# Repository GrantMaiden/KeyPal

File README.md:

KeyPal is A project I worked with during my undergrad alongside my teammates, Dane Le, Justin Warner, and Spencer Anderson.

I was the only EE working on the project, so my main duties were to develop the schematic and PCB for the group. I also developed the MCU application, and took care of component selection as well as analyzed and timing constraints on the system.

KeyPal is a fun solution to helping teach a new typist the ins and outs of proper keyboard hand placement.
It has capacitive sensors in the homerow of the keyboard, to make sure that proper hand placement is intact during typing, as well as multicolor LEDs under every key on the keyboard. These light up to aid the typist in learning the keypositions while using the peripheral typing trainer application, which is written in python.

________________________________________________________________________________________________________________________

Schematic creation, PCB layout, component selection, MCU design, C/C++, Python, timing analysis, Communication Protocols (i2c, USB),  capacitive touch.

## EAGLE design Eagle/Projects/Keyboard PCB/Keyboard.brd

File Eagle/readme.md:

Eagle Files and Libraries

Place in Users\<USER>\Documents\eagle

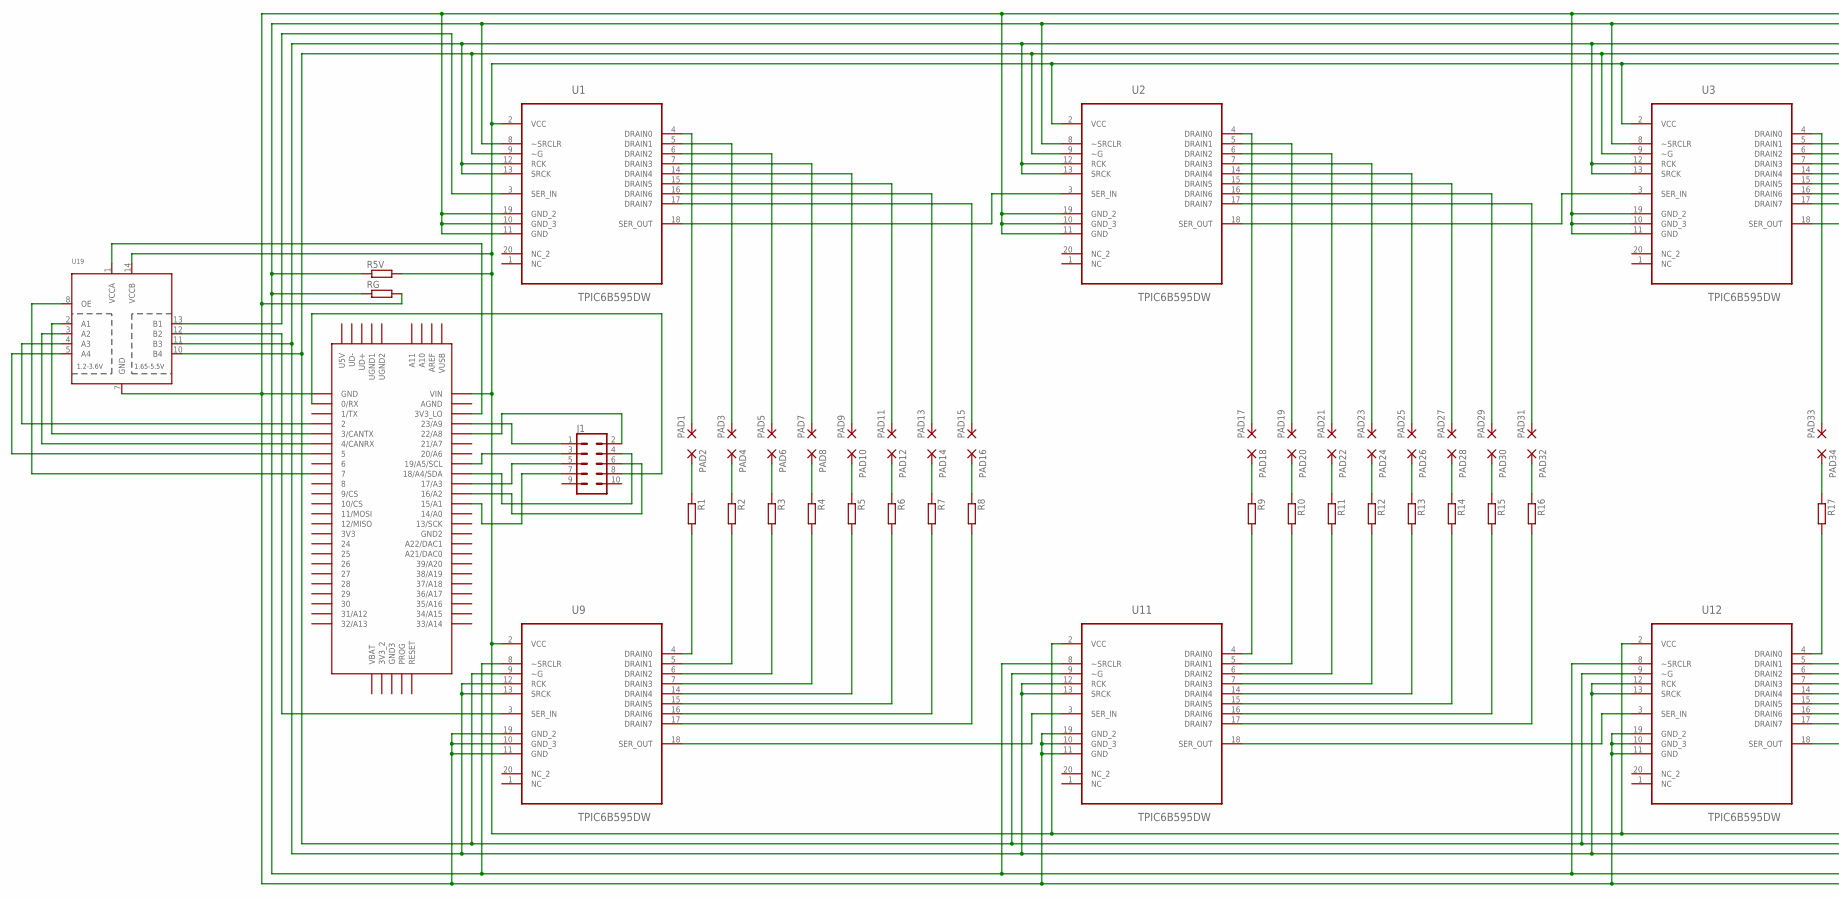
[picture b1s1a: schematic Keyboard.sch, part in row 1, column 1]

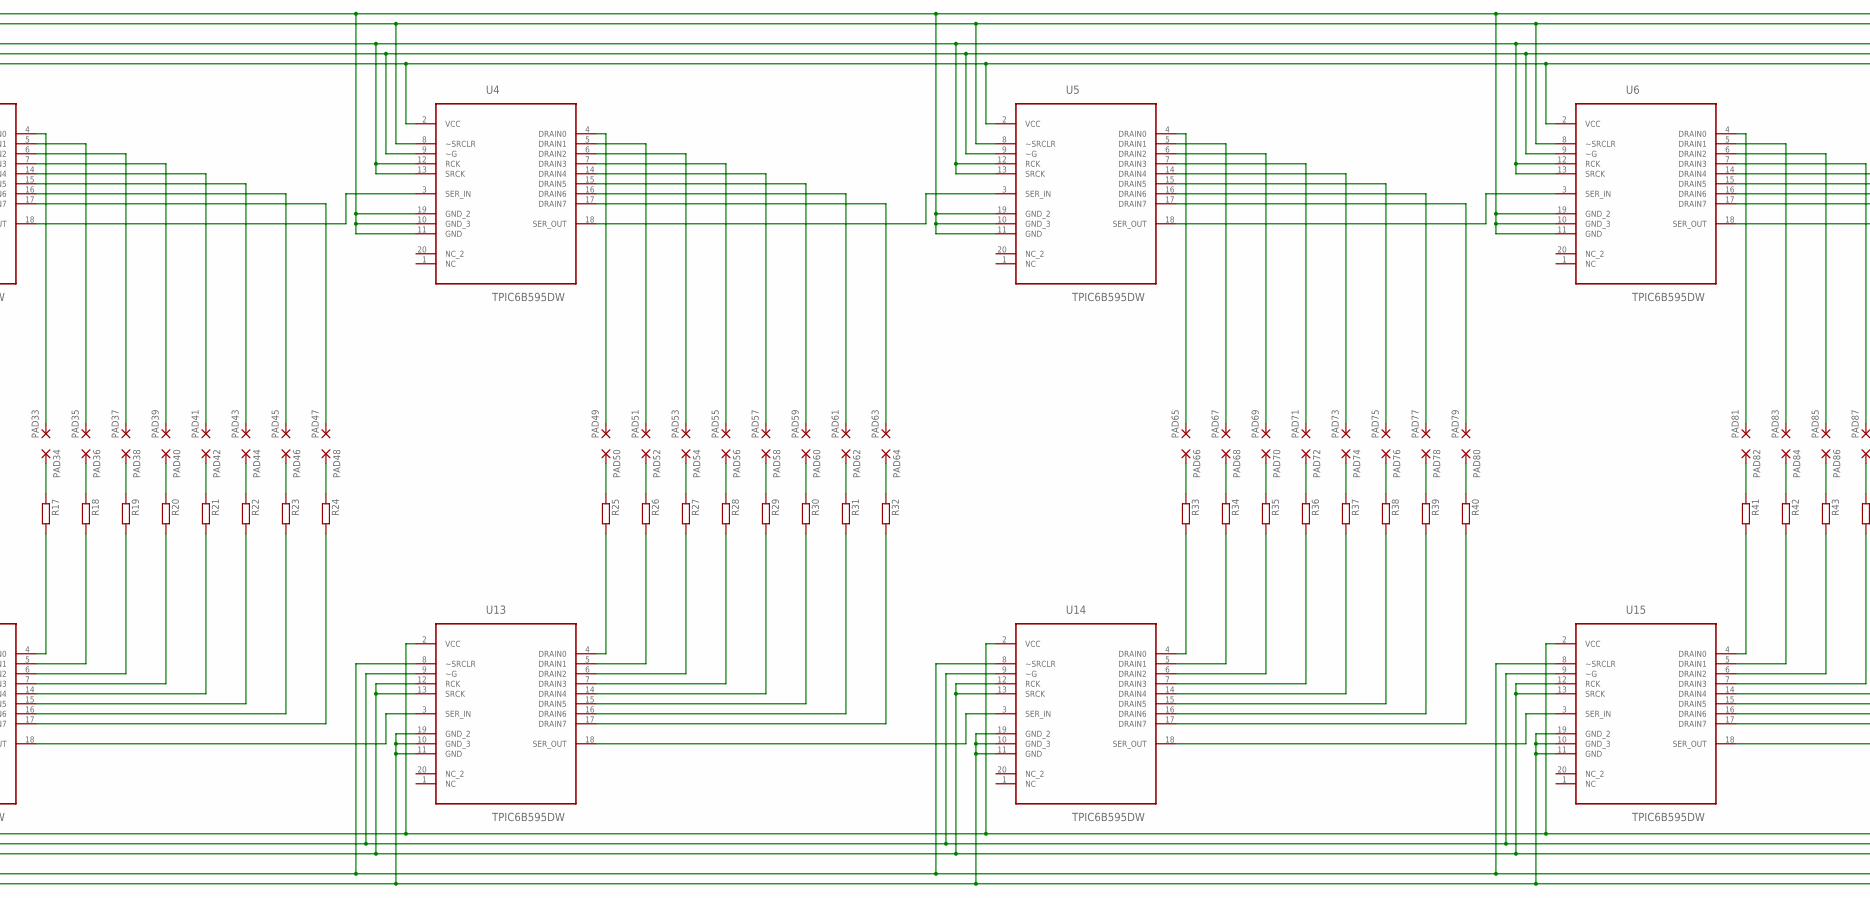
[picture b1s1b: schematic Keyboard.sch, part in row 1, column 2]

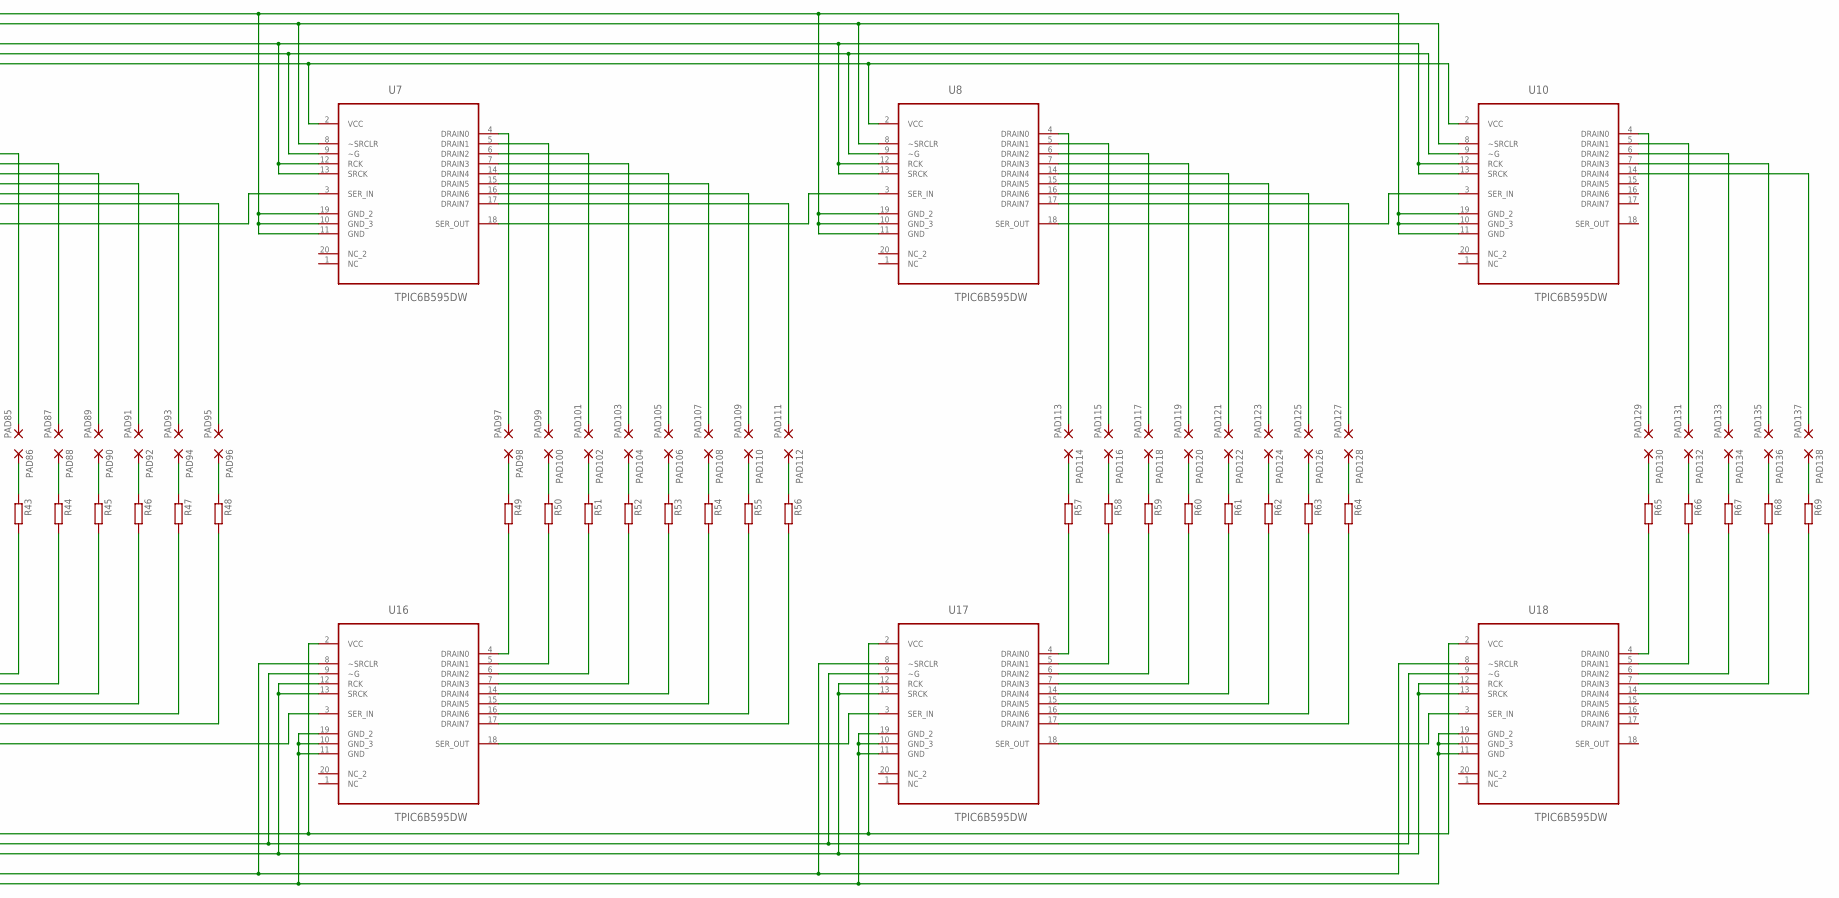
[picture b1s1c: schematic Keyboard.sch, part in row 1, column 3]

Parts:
J1: CONN_05X2SHD; 2X5-SHROUDED
PAD1, PAD2, PAD3, PAD4, PAD5, PAD6, PAD7, PAD8, PAD9, PAD10, PAD11, PAD12, PAD13, PAD14, PAD15, PAD16, PAD17, PAD18, PAD19, PAD20, PAD21, PAD22, PAD23, PAD24, PAD25, PAD26, PAD27, PAD28, PAD29, PAD30, PAD31, PAD32, PAD33, PAD34, PAD35, PAD36, PAD37, PAD38, PAD39, PAD40, PAD41, PAD42, PAD43, PAD44, PAD45, PAD46, PAD47, PAD48, PAD49, PAD50, PAD51, PAD52, PAD53, PAD54, PAD55, PAD56, PAD57, PAD58, PAD59, PAD60, PAD61, PAD62, PAD63, PAD64, PAD65, PAD66, PAD67, PAD68, PAD69, PAD70, PAD71, PAD72, PAD73, PAD74, PAD75, PAD76, PAD77, PAD78, PAD79, PAD80, PAD81, PAD82, PAD83, PAD84, PAD85, PAD86, PAD87, PAD88, PAD89, PAD90, PAD91, PAD92, PAD93, PAD94, PAD95, PAD96, PAD97, PAD98, PAD99, PAD100, PAD101, PAD102, PAD103, PAD104, PAD105, PAD106, PAD107, PAD108, PAD109, PAD110, PAD111, PAD112, PAD113, PAD114, PAD115, PAD116, PAD117, PAD118, PAD119, PAD120, PAD121, PAD122, PAD123, PAD124, PAD125, PAD126, PAD127, PAD128, PAD129, PAD130, PAD131, PAD132, PAD133, PAD134, PAD135, PAD136, PAD137, PAD138: 1,6/0,8
R1, R2, R3, R4, R5, R5V, R6, R7, R8, R9, R10, R11, R12, R13, R14, R15, R16, R17, R18, R19, R20, R21, R22, R23, R24, R25, R26, R27, R28, R29, R30, R31, R32, R33, R34, R35, R36, R37, R38, R39, R40, R41, R42, R43, R44, R45, R46, R47, R48, R49, R50, R51, R52, R53, R54, R55, R56, R57, R58, R59, R60, R61, R62, R63, R64, R65, R66, R67, R68, R69: R; R0805
RG: R; R0805
U1, U2, U3, U4, U5, U6, U7, U8, U9, U10, U11, U12, U13, U14, U15, U16, U17, U18: TPIC6B595DW; SOIC127P1030X265-20N
U19: TXB0104PWRSOIC14; SO14
U$59: TEENSY_3.5/3.6

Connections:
unnamed: PAD2.1, R1.1
unnamed: U1.18 (SER_OUT), U2.3 (SER_IN)
unnamed: U1.12 (RCK), U1.13 (SRCK), U2.12 (RCK), U2.13 (SRCK), U3.12 (RCK), U3.13 (SRCK), U4.12 (RCK), U4.13 (SRCK), U5.12 (RCK), U5.13 (SRCK), U6.12 (RCK), U6.13 (SRCK), U7.12 (RCK), U7.13 (SRCK), U8.12 (RCK), U8.13 (SRCK), U9.12 (RCK), U9.13 (SRCK), U10.12 (RCK), U10.13 (SRCK), U11.12 (RCK), U11.13 (SRCK), U12.12 (RCK), U12.13 (SRCK), U13.12 (RCK), U13.13 (SRCK), U14.12 (RCK), U14.13 (SRCK), U15.12 (RCK), U15.13 (SRCK), U16.12 (RCK), U16.13 (SRCK), U17.12 (RCK), U17.13 (SRCK), U18.12 (RCK), U18.13 (SRCK), U19.11 (B3)
unnamed: PAD4.1, R2.1
unnamed: PAD6.1, R3.1
unnamed: PAD8.1, R4.1
unnamed: PAD10.1, R5.1
unnamed: PAD12.1, R6.1
unnamed: PAD14.1, R7.1
unnamed: PAD16.1, R8.1
unnamed: PAD18.1, R9.1
unnamed: U1.9 (~G), U2.9 (~G), U3.9 (~G), U4.9 (~G), U5.9 (~G), U6.9 (~G), U7.9 (~G), U8.9 (~G), U9.9 (~G), U10.9 (~G), U11.9 (~G), U12.9 (~G), U13.9 (~G), U14.9 (~G), U15.9 (~G), U16.9 (~G), U17.9 (~G), U18.9 (~G), U19.10 (B4)
unnamed: PAD20.1, R10.1
unnamed: PAD22.1, R11.1
unnamed: PAD24.1, R12.1
unnamed: PAD26.1, R13.1
unnamed: PAD28.1, R14.1
unnamed: PAD30.1, R15.1
unnamed: PAD32.1, R16.1
unnamed: PAD34.1, R17.1
unnamed: PAD36.1, R18.1
unnamed: PAD38.1, R19.1
unnamed: PAD40.1, R20.1
unnamed: PAD42.1, R21.1
unnamed: PAD44.1, R22.1
unnamed: PAD46.1, R23.1
unnamed: PAD48.1, R24.1
unnamed: PAD50.1, R25.1
unnamed: PAD52.1, R26.1
unnamed: PAD54.1, R27.1
unnamed: PAD56.1, R28.1
unnamed: PAD58.1, R29.1
unnamed: PAD60.1, R30.1
unnamed: PAD62.1, R31.1
unnamed: PAD64.1, R32.1
unnamed: PAD66.1, R33.1
unnamed: PAD68.1, R34.1
unnamed: PAD70.1, R35.1
unnamed: PAD72.1, R36.1
unnamed: PAD74.1, R37.1
unnamed: PAD76.1, R38.1
unnamed: PAD78.1, R39.1
unnamed: PAD80.1, R40.1
unnamed: PAD82.1, R41.1
unnamed: PAD84.1, R42.1
unnamed: PAD86.1, R43.1
unnamed: PAD88.1, R44.1
unnamed: PAD90.1, R45.1
unnamed: PAD92.1, R46.1
unnamed: PAD94.1, R47.1
unnamed: PAD96.1, R48.1
unnamed: PAD98.1, R49.1
unnamed: PAD100.1, R50.1
unnamed: PAD102.1, R51.1
unnamed: PAD104.1, R52.1
unnamed: PAD106.1, R53.1
unnamed: PAD108.1, R54.1
unnamed: PAD110.1, R55.1
unnamed: PAD112.1, R56.1
unnamed: PAD114.1, R57.1
unnamed: R5V.2, U1.2 (VCC), U2.2 (VCC), U3.2 (VCC), U4.2 (VCC), U5.2 (VCC), U6.2 (VCC), U7.2 (VCC), U8.2 (VCC), U9.2 (VCC), U10.2 (VCC), U11.2 (VCC), U12.2 (VCC), U13.2 (VCC), U14.2 (VCC), U15.2 (VCC), U16.2 (VCC), U17.2 (VCC), U18.2 (VCC), U19.14 (VCCB), U$59.VIN
unnamed: U19.4 (A3), U$59.2
unnamed: R5V.1, RG.1, U1.8 (~SRCLR), U2.8 (~SRCLR), U3.8 (~SRCLR), U4.8 (~SRCLR), U5.8 (~SRCLR), U6.8 (~SRCLR), U7.8 (~SRCLR), U8.8 (~SRCLR), U9.8 (~SRCLR), U10.8 (~SRCLR), U11.8 (~SRCLR), U12.8 (~SRCLR), U13.8 (~SRCLR), U14.8 (~SRCLR), U15.8 (~SRCLR), U16.8 (~SRCLR), U17.8 (~SRCLR), U18.8 (~SRCLR)
unnamed: U1.3 (SER_IN), U19.13 (B1)
unnamed: U2.18 (SER_OUT), U3.3 (SER_IN)
unnamed: R68.2, U18.7 (DRAIN3)
unnamed: R69.2, U18.14 (DRAIN4)
unnamed: PAD129.1, U10.4 (DRAIN0)
unnamed: PAD131.1, U10.5 (DRAIN1)
unnamed: U3.18 (SER_OUT), U4.3 (SER_IN)
unnamed: U4.18 (SER_OUT), U5.3 (SER_IN)
unnamed: U5.18 (SER_OUT), U6.3 (SER_IN)
unnamed: U6.18 (SER_OUT), U7.3 (SER_IN)
unnamed: U7.18 (SER_OUT), U8.3 (SER_IN)
unnamed: U8.18 (SER_OUT), U10.3 (SER_IN)
unnamed: U19.1 (VCCA), U$59.3V3_LO
unnamed: U19.2 (A1), U$59.3/CANTX
unnamed: U9.3 (SER_IN), U19.12 (B2)
unnamed: U19.8 (OE), U$59.7
unnamed: PAD116.1, R58.1
unnamed: PAD118.1, R59.1
unnamed: PAD120.1, R60.1
unnamed: PAD122.1, R61.1
unnamed: PAD124.1, R62.1
unnamed: PAD126.1, R63.1
unnamed: PAD128.1, R64.1
unnamed: U9.18 (SER_OUT), U11.3 (SER_IN)
unnamed: U11.18 (SER_OUT), U12.3 (SER_IN)
unnamed: U12.18 (SER_OUT), U13.3 (SER_IN)
unnamed: U13.18 (SER_OUT), U14.3 (SER_IN)
unnamed: U14.18 (SER_OUT), U15.3 (SER_IN)
unnamed: U15.18 (SER_OUT), U16.3 (SER_IN)
unnamed: U16.18 (SER_OUT), U17.3 (SER_IN)
unnamed: U17.18 (SER_OUT), U18.3 (SER_IN)
unnamed: RG.2, U1.10 (GND_3), U1.11 (GND), U1.19 (GND_2), U2.10 (GND_3), U2.11 (GND), U2.19 (GND_2), U3.10 (GND_3), U3.11 (GND), U3.19 (GND_2), U4.10 (GND_3), U4.11 (GND), U4.19 (GND_2), U5.10 (GND_3), U5.11 (GND), U5.19 (GND_2), U6.10 (GND_3), U6.11 (GND), U6.19 (GND_2), U7.10 (GND_3), U7.11 (GND), U7.19 (GND_2), U8.10 (GND_3), U8.11 (GND), U8.19 (GND_2), U9.10 (GND_3), U9.11 (GND), U9.19 (GND_2), U10.10 (GND_3), U10.11 (GND), U10.19 (GND_2), U11.10 (GND_3), U11.11 (GND), U11.19 (GND_2), U12.10 (GND_3), U12.11 (GND), U12.19 (GND_2), U13.10 (GND_3), U13.11 (GND), U13.19 (GND_2), U14.10 (GND_3), U14.11 (GND), U14.19 (GND_2), U15.10 (GND_3), U15.11 (GND), U15.19 (GND_2), U16.10 (GND_3), U16.11 (GND), U16.19 (GND_2), U17.10 (GND_3), U17.11 (GND), U17.19 (GND_2), U18.10 (GND_3), U18.11 (GND), U18.19 (GND_2), U19.7 (GND), U$59.GND
unnamed: U19.5 (A4), U$59.5
unnamed: PAD130.1, R65.1
unnamed: PAD1.1, U1.4 (DRAIN0)
unnamed: PAD3.1, U1.5 (DRAIN1)
unnamed: PAD5.1, U1.6 (DRAIN2)
unnamed: PAD7.1, U1.7 (DRAIN3)
unnamed: PAD9.1, U1.14 (DRAIN4)
unnamed: PAD11.1, U1.15 (DRAIN5)
unnamed: PAD13.1, U1.16 (DRAIN6)
unnamed: PAD15.1, U1.17 (DRAIN7)
unnamed: R1.2, U9.4 (DRAIN0)
unnamed: R2.2, U9.5 (DRAIN1)
unnamed: R3.2, U9.6 (DRAIN2)
unnamed: R4.2, U9.7 (DRAIN3)
unnamed: R5.2, U9.14 (DRAIN4)
unnamed: R6.2, U9.15 (DRAIN5)
unnamed: R7.2, U9.16 (DRAIN6)
unnamed: R8.2, U9.17 (DRAIN7)
unnamed: R9.2, U11.4 (DRAIN0)
unnamed: R10.2, U11.5 (DRAIN1)
unnamed: R11.2, U11.6 (DRAIN2)
unnamed: R12.2, U11.7 (DRAIN3)
unnamed: R13.2, U11.14 (DRAIN4)
unnamed: R14.2, U11.15 (DRAIN5)
unnamed: R15.2, U11.16 (DRAIN6)
unnamed: R16.2, U11.17 (DRAIN7)
unnamed: PAD17.1, U2.4 (DRAIN0)
unnamed: PAD19.1, U2.5 (DRAIN1)
unnamed: PAD21.1, U2.6 (DRAIN2)
unnamed: PAD23.1, U2.7 (DRAIN3)
unnamed: PAD25.1, U2.14 (DRAIN4)
unnamed: PAD27.1, U2.15 (DRAIN5)
unnamed: PAD29.1, U2.16 (DRAIN6)
unnamed: PAD31.1, U2.17 (DRAIN7)
unnamed: PAD33.1, U3.4 (DRAIN0)
unnamed: PAD35.1, U3.5 (DRAIN1)
unnamed: PAD37.1, U3.6 (DRAIN2)
unnamed: PAD39.1, U3.7 (DRAIN3)
unnamed: PAD41.1, U3.14 (DRAIN4)
unnamed: PAD43.1, U3.15 (DRAIN5)
unnamed: PAD45.1, U3.16 (DRAIN6)
unnamed: PAD47.1, U3.17 (DRAIN7)
unnamed: R17.2, U12.4 (DRAIN0)
unnamed: R18.2, U12.5 (DRAIN1)
unnamed: R19.2, U12.6 (DRAIN2)
unnamed: R20.2, U12.7 (DRAIN3)
unnamed: R21.2, U12.14 (DRAIN4)
unnamed: R22.2, U12.15 (DRAIN5)
unnamed: R23.2, U12.16 (DRAIN6)
unnamed: R24.2, U12.17 (DRAIN7)
unnamed: R25.2, U13.4 (DRAIN0)
unnamed: R26.2, U13.5 (DRAIN1)
unnamed: R27.2, U13.6 (DRAIN2)
unnamed: U19.3 (A2), U$59.4/CANRX
unnamed: R28.2, U13.7 (DRAIN3)
unnamed: R29.2, U13.14 (DRAIN4)
unnamed: R30.2, U13.15 (DRAIN5)
unnamed: R31.2, U13.16 (DRAIN6)
unnamed: R32.2, U13.17 (DRAIN7)
unnamed: PAD49.1, U4.4 (DRAIN0)
unnamed: PAD51.1, U4.5 (DRAIN1)
unnamed: PAD53.1, U4.6 (DRAIN2)
unnamed: PAD55.1, U4.7 (DRAIN3)
unnamed: PAD57.1, U4.14 (DRAIN4)
unnamed: PAD59.1, U4.15 (DRAIN5)
unnamed: PAD61.1, U4.16 (DRAIN6)
unnamed: PAD63.1, U4.17 (DRAIN7)
unnamed: PAD65.1, U5.4 (DRAIN0)
unnamed: PAD67.1, U5.5 (DRAIN1)
unnamed: PAD69.1, U5.6 (DRAIN2)
unnamed: PAD71.1, U5.7 (DRAIN3)
unnamed: PAD73.1, U5.14 (DRAIN4)
unnamed: PAD75.1, U5.15 (DRAIN5)
unnamed: PAD77.1, U5.16 (DRAIN6)
unnamed: PAD79.1, U5.17 (DRAIN7)
unnamed: R33.2, U14.4 (DRAIN0)
unnamed: R34.2, U14.5 (DRAIN1)
unnamed: R35.2, U14.6 (DRAIN2)
unnamed: R36.2, U14.7 (DRAIN3)
unnamed: R37.2, U14.14 (DRAIN4)
unnamed: R38.2, U14.15 (DRAIN5)
unnamed: R39.2, U14.16 (DRAIN6)
unnamed: R40.2, U14.17 (DRAIN7)
unnamed: R41.2, U15.4 (DRAIN0)
unnamed: R42.2, U15.5 (DRAIN1)
unnamed: R43.2, U15.6 (DRAIN2)
unnamed: R44.2, U15.7 (DRAIN3)
unnamed: R45.2, U15.14 (DRAIN4)
unnamed: R46.2, U15.15 (DRAIN5)
unnamed: R47.2, U15.16 (DRAIN6)
unnamed: R48.2, U15.17 (DRAIN7)
unnamed: PAD81.1, U6.4 (DRAIN0)
unnamed: PAD83.1, U6.5 (DRAIN1)
unnamed: PAD85.1, U6.6 (DRAIN2)
unnamed: PAD87.1, U6.7 (DRAIN3)
unnamed: PAD89.1, U6.14 (DRAIN4)
unnamed: PAD91.1, U6.15 (DRAIN5)
unnamed: PAD93.1, U6.16 (DRAIN6)
unnamed: PAD95.1, U6.17 (DRAIN7)
unnamed: R49.2, U16.4 (DRAIN0)
unnamed: R50.2, U16.5 (DRAIN1)
unnamed: R51.2, U16.6 (DRAIN2)
unnamed: R52.2, U16.7 (DRAIN3)
unnamed: R53.2, U16.14 (DRAIN4)
unnamed: R54.2, U16.15 (DRAIN5)
unnamed: R55.2, U16.16 (DRAIN6)
unnamed: R56.2, U16.17 (DRAIN7)
unnamed: PAD97.1, U7.4 (DRAIN0)
unnamed: PAD99.1, U7.5 (DRAIN1)
unnamed: PAD101.1, U7.6 (DRAIN2)
unnamed: PAD103.1, U7.7 (DRAIN3)
unnamed: PAD105.1, U7.14 (DRAIN4)
unnamed: PAD107.1, U7.15 (DRAIN5)
unnamed: PAD109.1, U7.16 (DRAIN6)
unnamed: PAD111.1, U7.17 (DRAIN7)
unnamed: PAD113.1, U8.4 (DRAIN0)
unnamed: PAD115.1, U8.5 (DRAIN1)
unnamed: PAD117.1, U8.6 (DRAIN2)
unnamed: PAD119.1, U8.7 (DRAIN3)
unnamed: PAD121.1, U8.14 (DRAIN4)
unnamed: PAD123.1, U8.15 (DRAIN5)
unnamed: PAD125.1, U8.16 (DRAIN6)
unnamed: PAD127.1, U8.17 (DRAIN7)
unnamed: R57.2, U17.4 (DRAIN0)
unnamed: R58.2, U17.5 (DRAIN1)
unnamed: R59.2, U17.6 (DRAIN2)
unnamed: R60.2, U17.7 (DRAIN3)
unnamed: R61.2, U17.14 (DRAIN4)
unnamed: R62.2, U17.15 (DRAIN5)
unnamed: R63.2, U17.16 (DRAIN6)
unnamed: R64.2, U17.17 (DRAIN7)
unnamed: R65.2, U18.4 (DRAIN0)
unnamed: R66.2, U18.5 (DRAIN1)
unnamed: R67.2, U18.6 (DRAIN2)
unnamed: PAD132.1, R66.1
unnamed: PAD134.1, R67.1
unnamed: PAD136.1, R68.1
unnamed: PAD138.1, R69.1
unnamed: PAD133.1, U10.6 (DRAIN2)
unnamed: PAD135.1, U10.7 (DRAIN3)
unnamed: PAD137.1, U10.14 (DRAIN4)
unnamed: J1.1, U$59.23/A9
unnamed: J1.2, U$59.22/A8
unnamed: J1.3, U$59.19/A5/SCL
unnamed: J1.4, U$59.18/A4/SDA
unnamed: J1.5, U$59.17/A3
unnamed: J1.6, U$59.16/A2
unnamed: J1.7, U$59.15/A1
unnamed: J1.8, U$59.0/RX

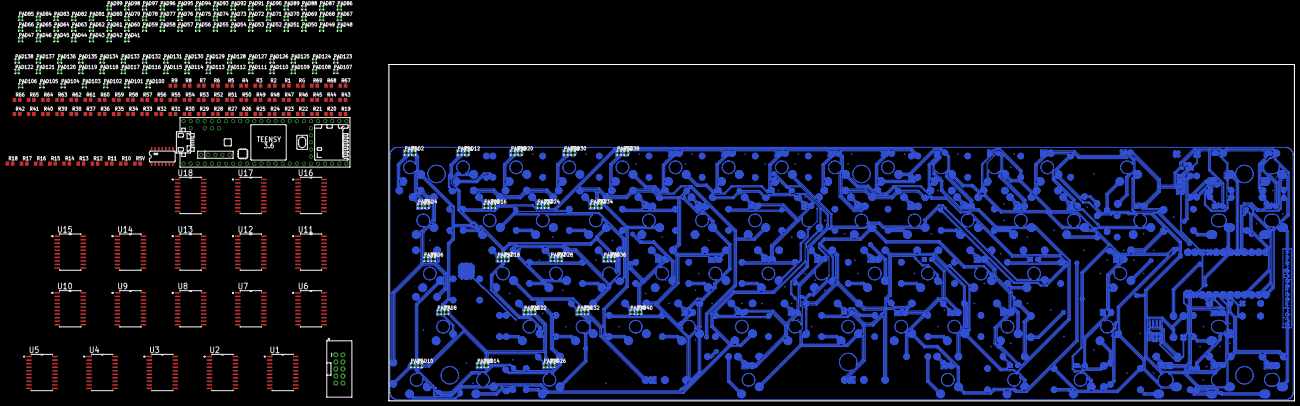
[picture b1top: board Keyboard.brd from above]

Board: 2 copper layers, 324.8 x 120.6 mm, 230 parts (0 on the bottom side), 244 nets.

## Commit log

2019-03-15 Bulk Upload
2019-03-15 Update Eagle Keyboard Files

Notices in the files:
parts and their libraries:
SparkFun-Connectors: Licensing: Creative Commons ShareAlike 4.0 International - https://creativecommons.org/licenses/by-sa/4.0
